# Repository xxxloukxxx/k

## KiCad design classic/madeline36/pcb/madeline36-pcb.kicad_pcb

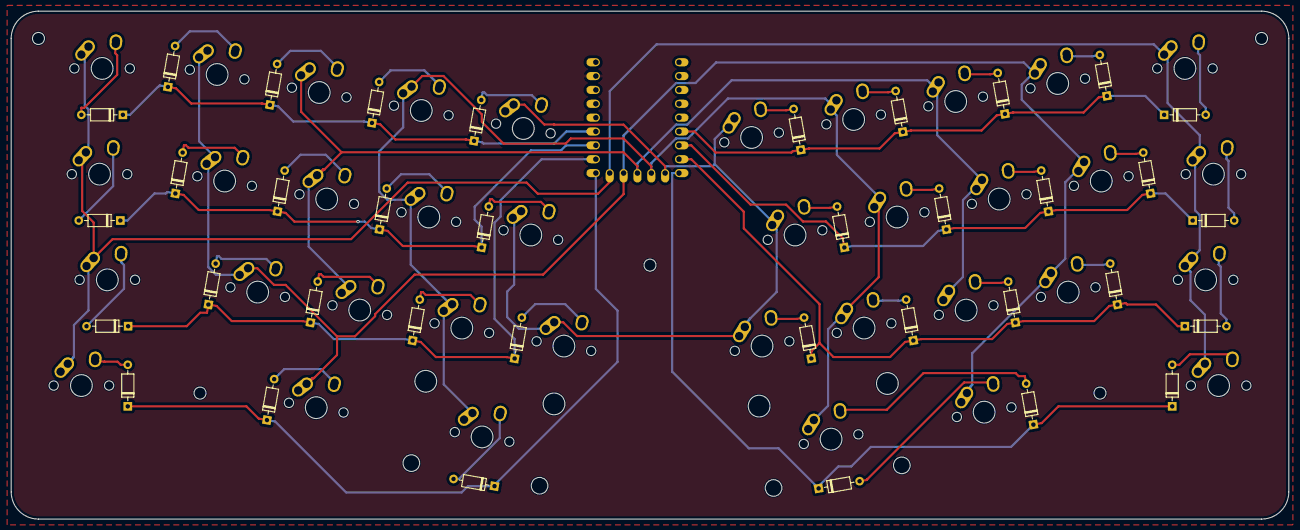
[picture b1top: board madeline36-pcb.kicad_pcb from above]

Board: 2 copper layers, 234.2 x 93.1 mm, 78 parts (0 on the bottom side), 49 nets.

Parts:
D1, D2, D3, D4, D5, D6, D7, D8, D9, D10, D11, D12, D13, D14, D15, D16, D17, D18, D19, D20, D21, D22, D23, D24, D25, D26, D27, D28, D29, D30, D31, D32, D33, D34, D35, D36: 1N4148; D_DO-35_SOD27_P7.62mm_Horizontal
H1, H2, H3, H4, H5: MountingHole; MountingHole_2.2mm_M2
SW1, SW2, SW3, SW4, SW5, SW6, SW7, SW8, SW9, SW12, SW13, SW14, SW15, SW16, SW17, SW18, SW19, SW20, SW22, SW23, SW24, SW25, SW26, SW27, SW28, SW29, SW31, SW32, SW35, SW36: SW_SPST; MX-Alps-Hybrid-1U
SW10, SW11: SW_SPST; MX-Alps-Hybrid-1.25U
SW21: SW_SPST; MX-Alps-Hybrid-1.75U
SW30: SW_SPST; MX-Alps-Hybrid-1.5U
SW33: SW_SPST; MX-Alps-Hybrid-2.25U-ReversedStabilizers
SW34: SW_SPST; MX-Alps-Hybrid-2U-ReversedStabilizers
U1: rp2040-zero; rp2040-zero-tht

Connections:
unnamed: D1.2 (A), SW1.2 (B)
unnamed: D2.2 (A), SW2.2 (B)
unnamed: D3.2 (A), SW3.2 (B)
unnamed: D4.2 (A), SW4.2 (B)
unnamed: D5.2 (A), SW5.2 (B)
unnamed: D6.2 (A), SW6.2 (B)
unnamed: D7.2 (A), SW7.2 (B)
unnamed: D8.2 (A), SW8.2 (B)
unnamed: D9.2 (A), SW9.2 (B)
unnamed: D10.2 (A), SW10.2 (B)
unnamed: D11.2 (A), SW11.2 (B)
unnamed: D12.2 (A), SW12.2 (B)
unnamed: D13.2 (A), SW13.2 (B)
unnamed: D14.2 (A), SW14.2 (B)
unnamed: D15.2 (A), SW15.2 (B)
unnamed: D16.2 (A), SW16.2 (B)
unnamed: D17.2 (A), SW17.2 (B)
unnamed: D18.2 (A), SW18.2 (B)
unnamed: D19.2 (A), SW19.2 (B)
unnamed: D20.2 (A), SW20.2 (B)
unnamed: D21.2 (A), SW21.2 (B)
unnamed: D22.2 (A), SW22.2 (B)
unnamed: D23.2 (A), SW23.2 (B)
unnamed: D24.2 (A), SW24.2 (B)
unnamed: D25.2 (A), SW25.2 (B)
unnamed: D26.2 (A), SW26.2 (B)
unnamed: D27.2 (A), SW27.2 (B)
unnamed: D28.2 (A), SW28.2 (B)
unnamed: D29.2 (A), SW29.2 (B)
unnamed: D30.2 (A), SW30.2 (B)
unnamed: D31.2 (A), SW31.2 (B)
unnamed: D32.2 (A), SW32.2 (B)
unnamed: D33.2 (A), SW33.2 (B)
unnamed: D34.2 (A), SW34.2 (B)
unnamed: D35.2 (A), SW35.2 (B)
unnamed: D36.2 (A), SW36.2 (B)
c0: SW1.1 (A), SW10.1 (A), SW11.1 (A), SW20.1 (A), SW21.1 (A), SW30.1 (A), SW31.1 (A), SW36.1 (A), U1.14 (13)
c1: SW2.1 (A), SW9.1 (A), SW12.1 (A), SW19.1 (A), SW22.1 (A), SW29.1 (A), SW32.1 (A), SW35.1 (A), U1.13 (12)
c2: SW3.1 (A), SW8.1 (A), SW13.1 (A), SW18.1 (A), SW23.1 (A), SW28.1 (A), U1.12 (11)
c3: SW4.1 (A), SW7.1 (A), SW14.1 (A), SW17.1 (A), SW24.1 (A), SW27.1 (A), SW33.1 (A), SW34.1 (A), U1.11 (10)
c4: SW5.1 (A), SW6.1 (A), SW15.1 (A), SW16.1 (A), SW25.1 (A), SW26.1 (A), U1.10 (9)
l0: D1.1 (K), D2.1 (K), D3.1 (K), D4.1 (K), D5.1 (K), U1.18 (27)
l1: D11.1 (K), D12.1 (K), D13.1 (K), D14.1 (K), D15.1 (K), U1.17 (26)
l2: D21.1 (K), D22.1 (K), D23.1 (K), D24.1 (K), D25.1 (K), U1.16 (15)
l3: D31.1 (K), D32.1 (K), D33.1 (K), U1.15 (14)
l4: D34.1 (K), D35.1 (K), D36.1 (K), U1.9 (8)
l5: D26.1 (K), D27.1 (K), D28.1 (K), D29.1 (K), D30.1 (K), U1.8 (7)
l6: D16.1 (K), D17.1 (K), D18.1 (K), D19.1 (K), D20.1 (K), U1.7 (6)
l7: D6.1 (K), D7.1 (K), D8.1 (K), D9.1 (K), D10.1 (K), U1.6 (5)

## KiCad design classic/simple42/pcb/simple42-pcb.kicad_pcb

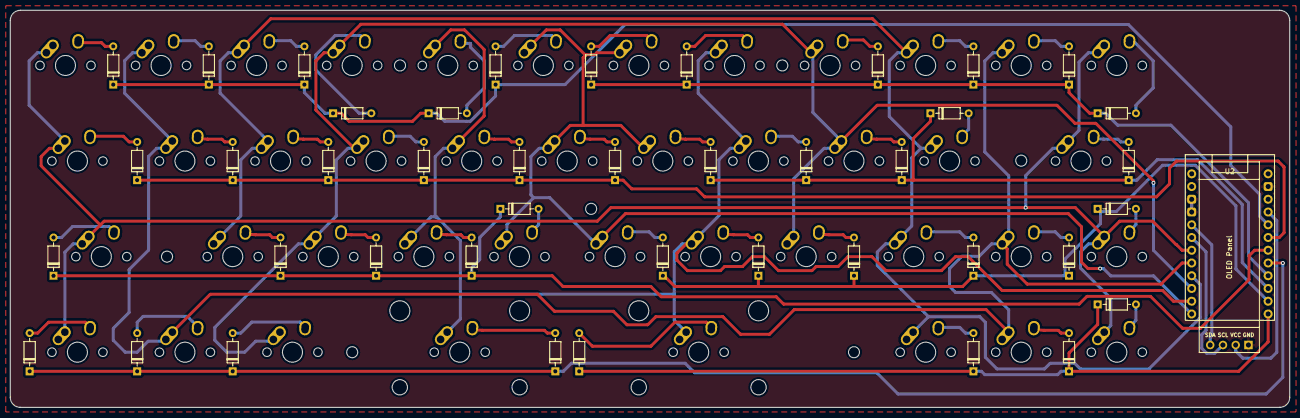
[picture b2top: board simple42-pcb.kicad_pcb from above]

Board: 2 copper layers, 255.0 x 79.1 mm, 93 parts (0 on the bottom side), 60 nets.

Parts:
D1, D2, D3, D4, D5, D6, D7, D8, D9, D10, D11, D12, D13, D14, D15, D16, D17, D18, D19, D20, D21, D22, D23, D24, D25, D26, D27, D28, D29, D30, D31, D32, D33, D34, D35, D36, D37, D38, D39, D40, D41, D42: 1N4148; D_DO-35_SOD27_P7.62mm_Horizontal
H1, H2, H3, H4, H5, H6, H7: MountingHole; MountingHole_2.2mm_M2
MX1, MX2, MX3, MX4, MX5, MX6, MX7, MX8, MX9, MX10, MX11, MX12, MX14, MX15, MX16, MX17, MX18, MX19, MX20, MX21, MX22, MX25, MX26, MX27, MX28, MX29, MX30, MX31, MX33, MX34, MX36, MX40, MX41, MX42: MX; MX-Alps-Hybrid-1U
MX13, MX32, MX35, MX37: MX; MX-Alps-Hybrid-1.25U
MX23, MX24: MX; MX-Alps-Hybrid-1.75U
MX38: MX; MX-Alps-Hybrid-2.25U-ReversedStabilizers
MX39: MX; MX-Alps-Hybrid-2.75U-ReversedStabilizers
U1: ProMicro; ProMicro_USBup
U2: SSD1306; SSD1306-0.91-OLED-4pin-128x32

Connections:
C0: MX1.1 (COL), MX12.1 (COL), MX13.1 (COL), MX23.1 (COL), MX24.1 (COL), MX34.1 (COL), MX35.1 (COL), MX42.1 (COL), U1.7 (D4)
C1: MX2.1 (COL), MX11.1 (COL), MX14.1 (COL), MX33.1 (COL), MX36.1 (COL), MX41.1 (COL), U1.8 (C6)
C2: MX3.1 (COL), MX10.1 (COL), MX15.1 (COL), MX22.1 (COL), MX25.1 (COL), MX32.1 (COL), MX40.1 (COL), U1.9 (D7)
C3: MX4.1 (COL), MX9.1 (COL), MX16.1 (COL), MX21.1 (COL), MX26.1 (COL), MX31.1 (COL), MX37.1 (COL), U1.10 (E6)
C4: MX5.1 (COL), MX8.1 (COL), MX17.1 (COL), MX20.1 (COL), MX27.1 (COL), MX30.1 (COL), MX38.1 (COL), MX39.1 (COL), U1.11 (B4)
C5: MX6.1 (COL), MX7.1 (COL), MX18.1 (COL), MX19.1 (COL), MX28.1 (COL), MX29.1 (COL), U1.12 (B5)
GND: U1.3 (GND), U1.4 (GND), U1.14 (GND), U2.1 (GND)
L0: D1.1 (K), D2.1 (K), D3.1 (K), D4.1 (K), D5.1 (K), D6.1 (K), U1.17 (F4)
L1: D7.1 (K), D8.1 (K), D9.1 (K), D10.1 (K), D11.1 (K), D12.1 (K), U1.21 (B1)
L2: D13.1 (K), D14.1 (K), D15.1 (K), D16.1 (K), D17.1 (K), D18.1 (K), U1.18 (F5)
L3: D19.1 (K), D20.1 (K), D21.1 (K), D22.1 (K), D23.1 (K), U1.22 (B3)
L4: D24.1 (K), D25.1 (K), D26.1 (K), D27.1 (K), D28.1 (K), U1.19 (F6)
L5: D29.1 (K), D30.1 (K), D31.1 (K), D32.1 (K), D33.1 (K), D34.1 (K), U1.23 (B2)
L6: D35.1 (K), D36.1 (K), D37.1 (K), D38.1 (K), U1.20 (F7)
L7: D39.1 (K), D40.1 (K), D41.1 (K), D42.1 (K), U1.24 (B6)
unnamed: D1.2 (A), MX1.2 (ROW)
unnamed: D2.2 (A), MX2.2 (ROW)
unnamed: D3.2 (A), MX3.2 (ROW)
unnamed: D4.2 (A), MX4.2 (ROW)
unnamed: D5.2 (A), MX5.2 (ROW)
unnamed: D6.2 (A), MX6.2 (ROW)
unnamed: D7.2 (A), MX7.2 (ROW)
unnamed: D8.2 (A), MX8.2 (ROW)
unnamed: D9.2 (A), MX9.2 (ROW)
unnamed: D10.2 (A), MX10.2 (ROW)
unnamed: D11.2 (A), MX11.2 (ROW)
unnamed: D12.2 (A), MX12.2 (ROW)
unnamed: D13.2 (A), MX13.2 (ROW)
unnamed: D14.2 (A), MX14.2 (ROW)
unnamed: D15.2 (A), MX15.2 (ROW)
unnamed: D16.2 (A), MX16.2 (ROW)
unnamed: D17.2 (A), MX17.2 (ROW)
unnamed: D18.2 (A), MX18.2 (ROW)
unnamed: D19.2 (A), MX19.2 (ROW)
unnamed: D20.2 (A), MX20.2 (ROW)
unnamed: D21.2 (A), MX21.2 (ROW)
unnamed: D22.2 (A), MX22.2 (ROW)
unnamed: D23.2 (A), MX23.2 (ROW)
unnamed: D24.2 (A), MX24.2 (ROW)
unnamed: D25.2 (A), MX25.2 (ROW)
unnamed: D26.2 (A), MX26.2 (ROW)
unnamed: D27.2 (A), MX27.2 (ROW)
unnamed: D28.2 (A), MX28.2 (ROW)
unnamed: D29.2 (A), MX29.2 (ROW)
unnamed: D30.2 (A), MX30.2 (ROW)
unnamed: D31.2 (A), MX31.2 (ROW)
unnamed: D32.2 (A), MX32.2 (ROW)
unnamed: D33.2 (A), MX33.2 (ROW)
unnamed: D34.2 (A), MX34.2 (ROW)
unnamed: D35.2 (A), MX35.2 (ROW)
unnamed: D36.2 (A), MX36.2 (ROW)
unnamed: D37.2 (A), MX37.2 (ROW)
unnamed: D38.2 (A), MX38.2 (ROW)
unnamed: D39.2 (A), MX39.2 (ROW)
unnamed: D40.2 (A), MX40.2 (ROW)
unnamed: D41.2 (A), MX41.2 (ROW)
unnamed: D42.2 (A), MX42.2 (ROW)
unnamed: U1.6 (D0), U2.3 (SCL)
unnamed: U1.5 (D1), U2.4 (SDA)
VCC: U1.16 (VCC), U2.2 (VCC)
